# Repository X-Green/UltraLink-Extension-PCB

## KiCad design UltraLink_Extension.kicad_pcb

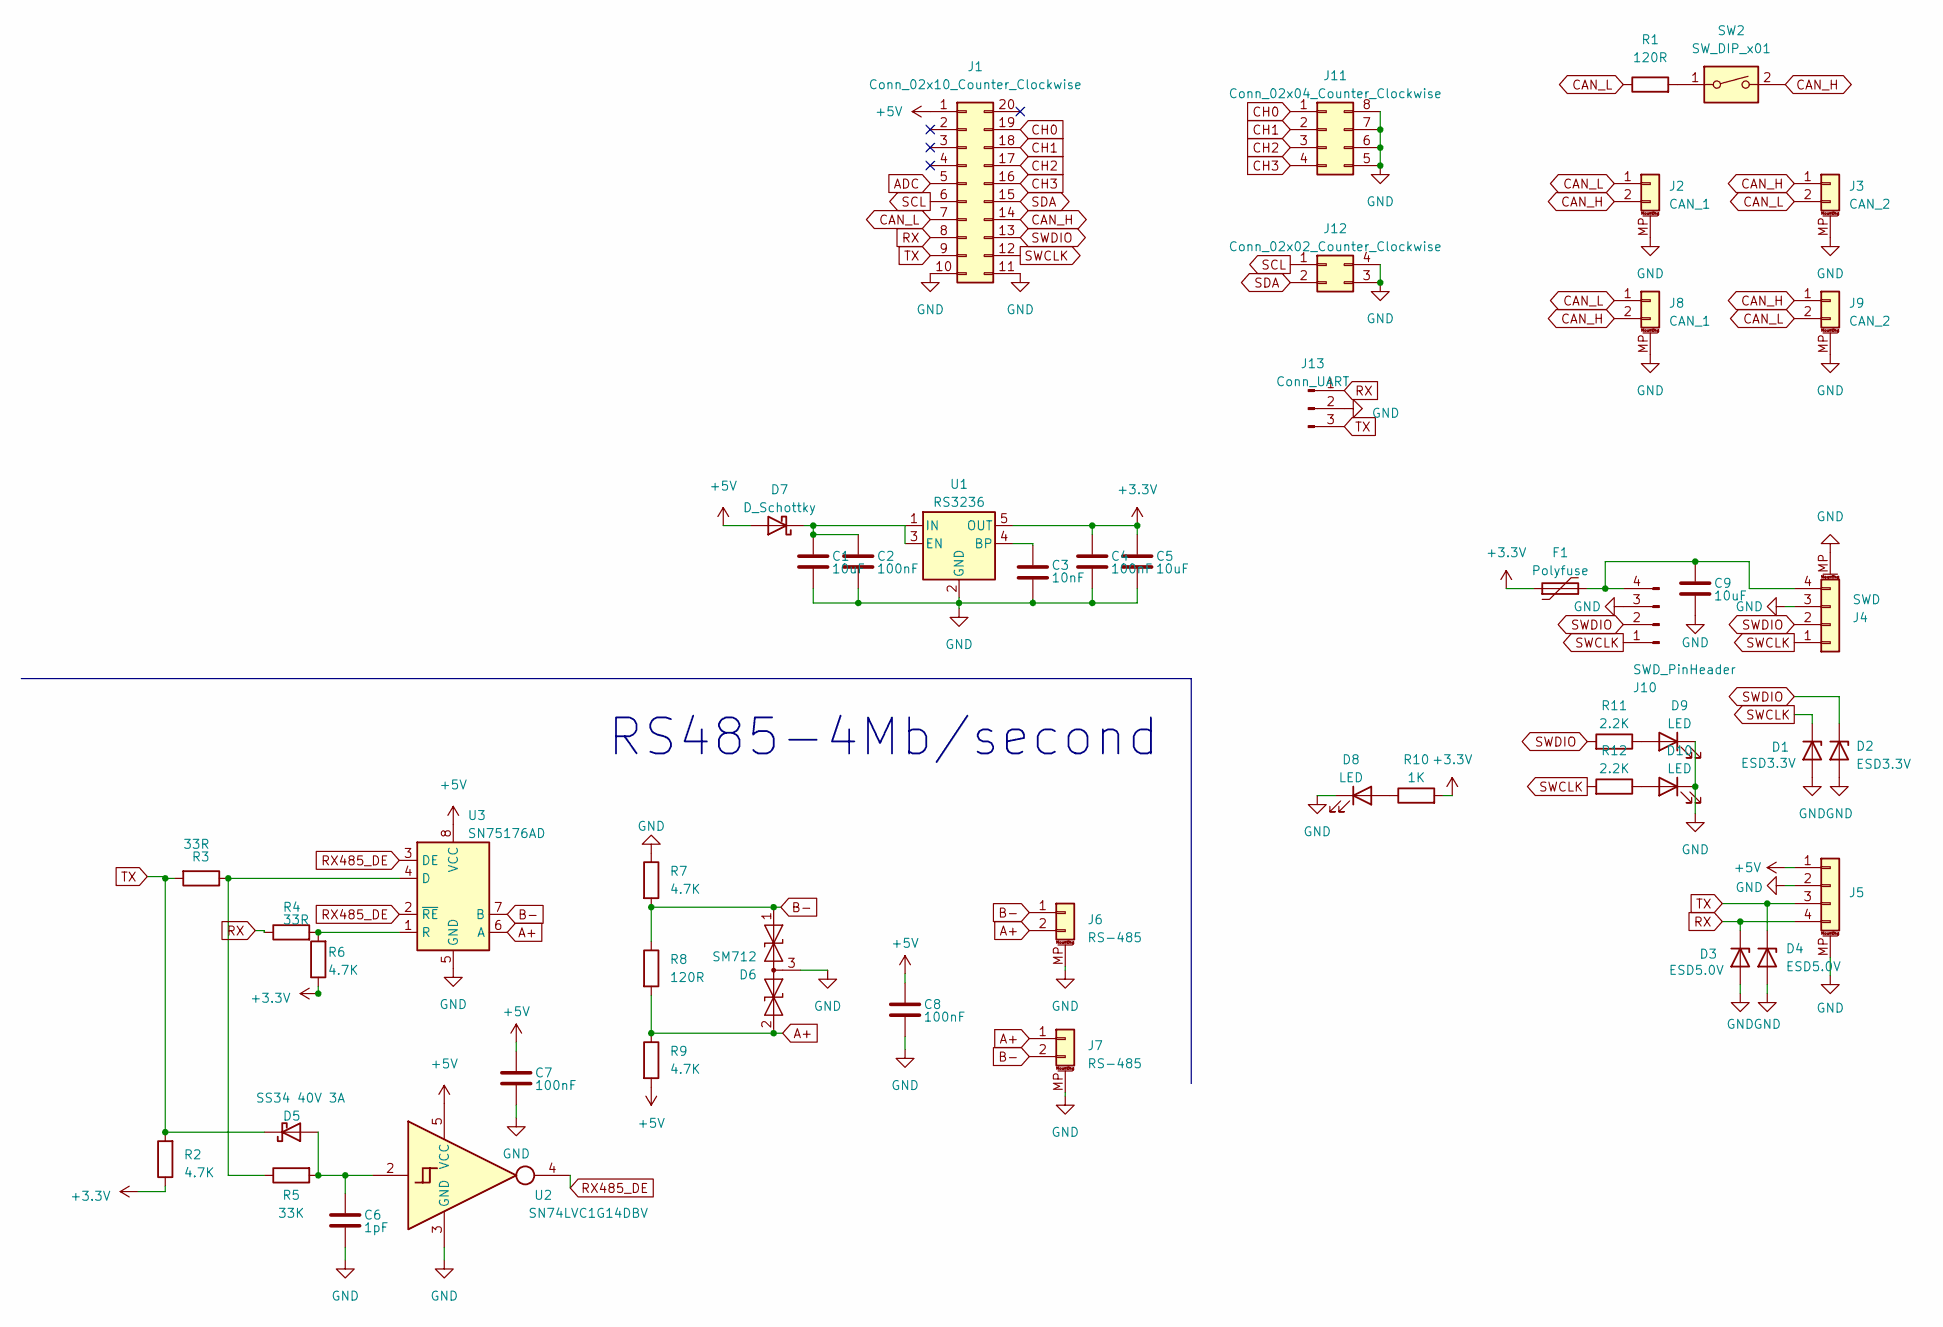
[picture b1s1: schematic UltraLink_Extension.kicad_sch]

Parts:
C1, C5, C9: 10uF; C_1206_3216Metric
C2, C4, C7, C8: 100nF; C_0603_1608Metric
C3: 10nF; C_0603_1608Metric
C6: 1pF; C_0603_1608Metric
D1, D2: ESD3.3V; D_SOD-323_HandSoldering
D3, D4: ESD5.0V; D_SOD-323_HandSoldering
D5: SS34 40V 3A; D_SMF
D6: SM712; SOT-23
D7: D_Schottky; D_SMF
D8, D9, D10: LED; LED_0603_1608Metric
F1: Polyfuse; Fuse_0805_2012Metric_Pad1.15x1.40mm_HandSolder
J1: Conn_02x10_Counter_Clockwise; PinHeader_2x10_P2.54mm_Vertical
J2, J8: CAN_1; JST_GH_SM02B-GHS-TB_1x02-1MP_P1.25mm_Horizontal
J3, J9: CAN_2; JST_GH_SM02B-GHS-TB_1x02-1MP_P1.25mm_Horizontal
J4: SWD; Molex_PicoBlade_53261-0471_1x04-1MP_P1.25mm_Horizontal
J5: Conn_01x04_MountingPin; JST_GH_BM04B-GHS-TBT_1x04-1MP_P1.25mm_Vertical
J6: RS-485; JST_GH_BM02B-GHS-TBT_1x02-1MP_P1.25mm_Vertical
J7: RS-485; JST_GH_SM02B-GHS-TB_1x02-1MP_P1.25mm_Horizontal
J10: SWD_PinHeader; PinHeader_1x04_P2.54mm_Horizontal
J11: Conn_02x04_Counter_Clockwise; PinHeader_2x04_P2.54mm_Horizontal
J12: Conn_02x02_Counter_Clockwise; PinHeader_2x02_P2.54mm_Horizontal
J13: Conn_UART; PinSocket_1x03_P2.54mm_Horizontal
R1, R8: 120R; R_0603_1608Metric
R2, R6, R7, R9: 4.7K; R_0603_1608Metric
R3, R4: 33R; R_0603_1608Metric
R5: 33K; R_0603_1608Metric
R10: 1K; R_0603_1608Metric
R11, R12: 2.2K; R_0603_1608Metric
SW2: SW_DIP_x01; SW_DIP_SPSTx01_Slide_9.78x4.72mm_W8.61mm_P2.54mm
U1: RS3236; SOT-23-5
U2: SN74LVC1G14DBV; SOT-23-5
U3: SN75176AD; SOIC-8_3.9x4.9mm_P1.27mm

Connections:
+3.3V: C4.1, C5.1, F1.1, R2.1, R6.1, R10.2, U1.5 (OUT)
+5V: C7.1, C8.1, D7.2 (A), J1.1, J5.1, R9.2, U2.5 (VCC), U3.8 (VCC)
A+: D6.2 (A2), J6.2, J7.1, R8.2, R9.1, U3.6 (A)
ADC: J1.5
B-: D6.1 (A1), J6.1, J7.2, R7.2, R8.1, U3.7 (B)
CAN_H: J1.14, J2.2, J3.1, J8.2, J9.1, SW2.2
CAN_L: J1.7, J2.1, J3.2, J8.1, J9.2, R1.1
CH0: J1.19, J11.1
CH1: J1.18, J11.2
CH2: J1.17, J11.3
CH3: J1.16, J11.4
GND: C1.2, C2.2, C3.2, C4.2, C5.2, C6.2, C7.2, C8.2, C9.2, D1.2 (A), D2.2 (A), D3.2 (A), D4.2 (A), D6.3 (common), D8.1 (K), D9.1 (K), D10.1 (K), J1.10, J1.11, J2.MP (MountPin), J3.MP (MountPin), J4.3, J4.MP (MountPin), J5.2, J5.MP (MountPin), J6.MP (MountPin), J7.MP (MountPin), J8.MP (MountPin), J9.MP (MountPin), J10.3, J11.5, J11.6, J11.7, J11.8, J12.3, J12.4, J13.2, R7.1, U1.2 (GND), U2.3 (GND), U3.5 (GND)
unnamed: C6.1, D5.2 (A), R5.2, U2.2
unnamed: C1.1, C2.1, D7.1 (K), U1.1 (IN), U1.3 (EN)
unnamed: D8.2 (A), R10.1
unnamed: D9.2 (A), R11.1
unnamed: D10.2 (A), R12.1
unnamed: C9.1, F1.2, J4.4, J10.4
unnamed: R1.2, SW2.1
unnamed: C3.1, U1.4 (BP)
unnamed: R3.1, R5.1, U3.4 (D)
unnamed: R4.2, R6.2, U3.1 (R)
RX: D3.1 (K), J1.8, J5.4, J13.1, R4.1
RX485_DE: U2.4, U3.2 (~RE), U3.3 (DE)
SCL: J1.6, J12.1
SDA: J1.15, J12.2
SWCLK: D1.1 (K), J1.12, J4.1, J10.1, R12.2
SWDIO: D2.1 (K), J1.13, J4.2, J10.2, R11.2
TX: D4.1 (K), D5.1 (K), J1.9, J5.3, J13.3, R2.2, R3.2

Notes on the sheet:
RS485-4Mb/second

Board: 2 copper layers, 49 parts (1 on the bottom side), 28 nets, no tracks yet.

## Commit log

2023-09-04 Schemetics Done
2023-09-04 Add ignore
